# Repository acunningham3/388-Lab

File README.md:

# 388-Lab
Group Members:
Adam Cunningham,
Ryan McCarthy,
James McCarthy

Topic:
Automated Greenhouse Management System
  
  This is the repository for every lab report for our group.

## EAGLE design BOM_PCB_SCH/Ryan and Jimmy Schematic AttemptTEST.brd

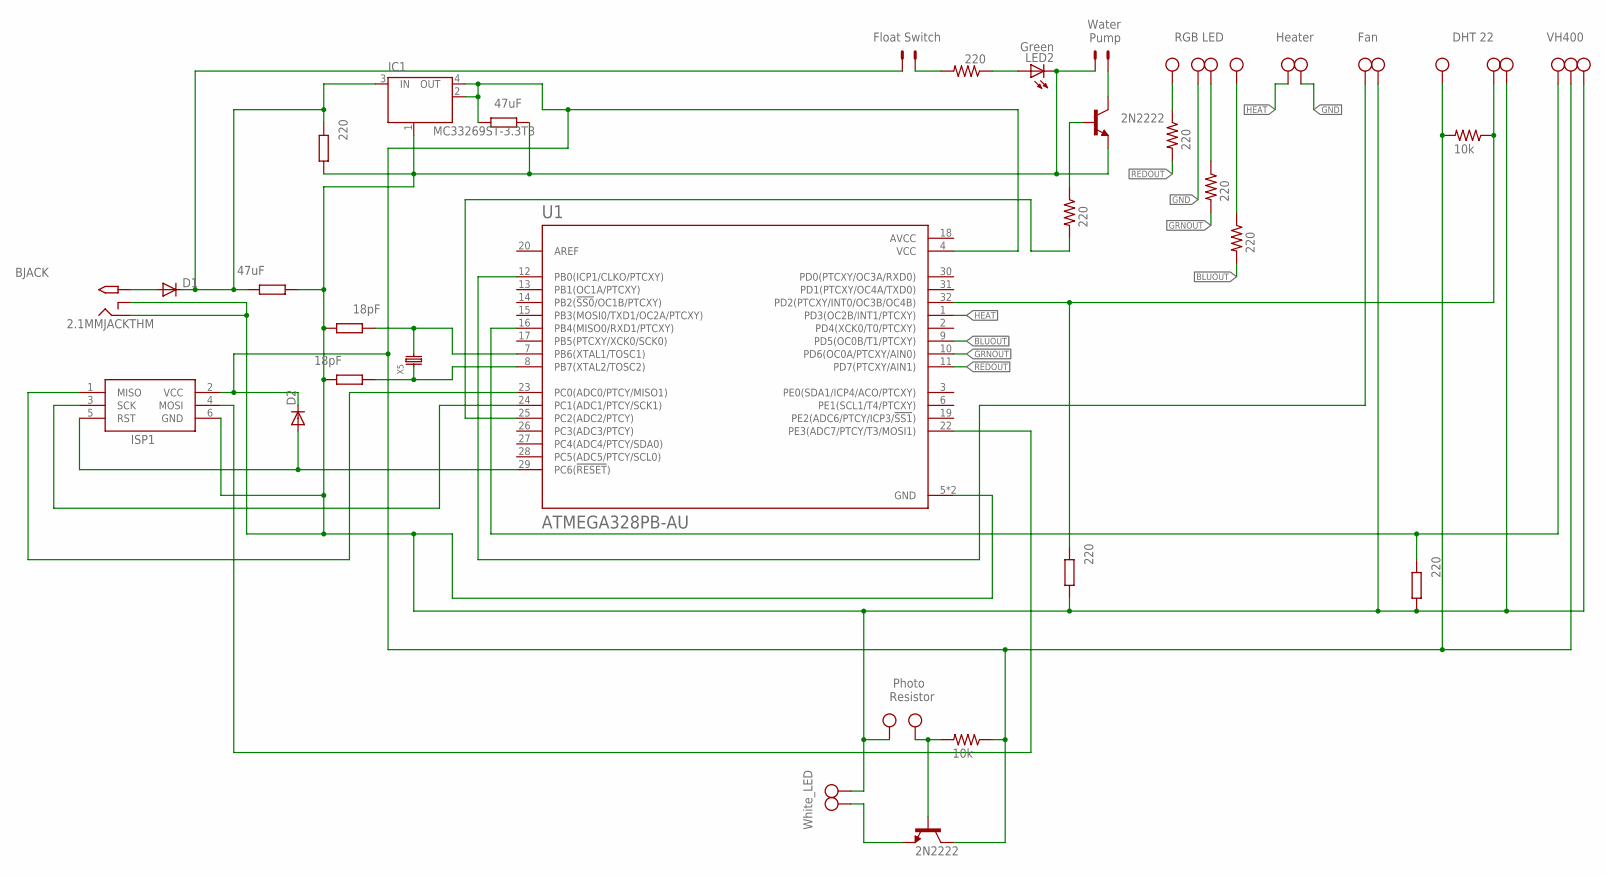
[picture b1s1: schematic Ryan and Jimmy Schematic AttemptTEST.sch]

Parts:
BJACK: 2.1MMJACKTHM; PJ-102A
C1, C6, C11: 220; M0805
C3, C8: 47uF; M0805
C9, C12: 18pF; M0805
D1, D2: DIODE-DO214BA; DO214BA
IC1: MC33269ST-3.3T3; SOT223
ISP1: AVRISP-6; AVRISP
LED2: Green; CHIPLED_0805
R1, R2, R4, R6, R7: 220; R0805
R3, R8: 10k; R0805
T1, T2: 2N2222; TO18
U1: ATMEGA328PB-AU; QFP80P900X900X120-32N
X1, X3: 1X03_5MM_SCREW; W237-103
X2, X4, X6, X8: 1X02_5MM_SCREW; W237-102
X5: ECS-80-18-5PX-TR; HC49/US
X7: W237-4
X9, X10: 332-02

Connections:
5V: C3.2, D2.C, IC1.2 (OUT), IC1.4 (OUT), ISP1.2 (VCC), R3.1, R8.2, T2.3 (C), U1.4 (VCC), X1.3, X3.2
AVCC: U1.18 (AVCC)
B: R7.1, X7.1
BLUOUT: R7.2, U1.9 (PD5(OC0B/T1/PTCXY))
DHT: C6.2, R8.1, U1.32 (PD2(PTCXY/INT0/OC3B/OC4B)), X1.2
FAN: U1.12 (PB0(ICP1/CLKO/PTCXY)), X8.2
F_S: R1.2, X10.1
G: R6.1, X7.2
GND: BJACK.RING, BJACK.RING_SW, C1.1, C3.1, C6.1, C8.1, C9.2, C11.1, C12.2, IC1.1 (GND/ADJ), ISP1.6 (GND), LED2.C, T1.1 (E), U1.5 (GND), U1.21 (GND), X1.1, X2.2, X3.1, X4.1, X6.2, X7.3, X8.1, X9.1
GRNOUT: R6.2, U1.10 (PD6(OC0A/PTCXY/AIN0))
HEAT: U1.1 (PD3(OC2B/INT1/PTCXY)), X4.2
MISO: ISP1.1 (MISO), U1.23 (PC0(ADC0/PTCY/MISO1))
MOSI: ISP1.4 (MOSI), U1.22 (PE3(ADC7/PTCY/T3/MOSI1))
unnamed: LED2.A, R1.1
PHOTO: R3.2, T2.2 (B), X2.1
POUT: R4.2, U1.25 (PC2(ADC2/PTCY))
PUMP: T1.3 (C), X9.2
PWRIN: BJACK.TIP, D1.A
P_CON: R4.1, T1.2 (B)
R: R2.1, X7.4
REDOUT: R2.2, U1.11 (PD7(PTCXY/AIN1))
RESET: D2.A, ISP1.5 (RST), U1.29 (PC6(!RESET!))
SCK: ISP1.3 (SCK), U1.24 (PC1(ADC1/PTCY/SCK1))
VH400: C11.2, U1.16 (PB4(MISO0/RXD1/PTCXY)), X3.3
VIN: C1.2, C8.2, D1.C, IC1.3 (IN), X10.2
WHT_LED: T2.1 (E), X6.1
XTAL1: C9.1, U1.7 (PB6(XTAL1/TOSC1)), X5.P$2 (XOUT)
XTAL2: C12.1, U1.8 (PB7(XTAL2/TOSC2)), X5.P$1 (XIN)

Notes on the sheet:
Fan
Heater
DHT 22
RGB LED
Water Pump
Float Switch
VH400
White_LED
Photo Resistor

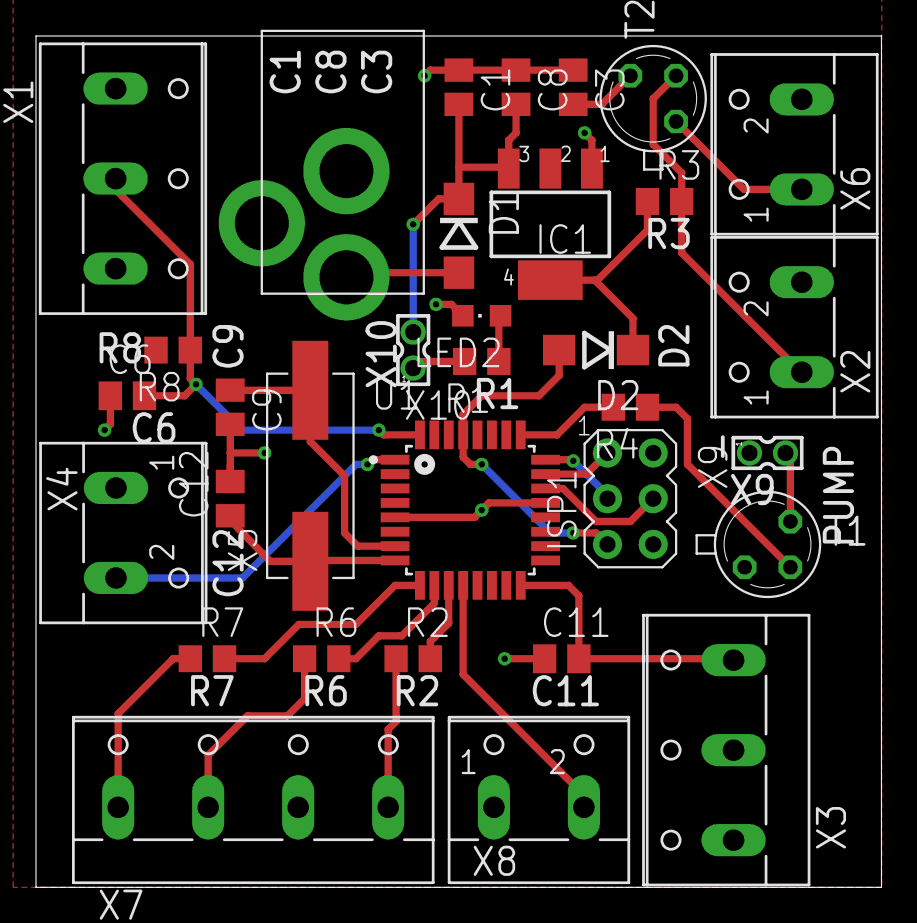
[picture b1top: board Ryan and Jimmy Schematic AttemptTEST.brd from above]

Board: 2 copper layers, 47.0 x 47.3 mm, 33 parts (0 on the bottom side), 27 nets.

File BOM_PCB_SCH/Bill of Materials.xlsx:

Qty | Value | Device | Package | Parts | Description | AVAILABILITY | DESCRIPTION | MF | MP | MPN | OC_FARNELL | OC_NEWARK | PACKAGE
4 |  | 1X02_5MM_SCREW | W237-102 | X2
2 |  | 1X03_5MM_SCREW | W237-103 | X1
2 |  | DIODE-DO214BA | DO214BA | D1
1 |  | ECS-80-18-5PX-TR | HC49/US | X5
1 |  | W237-4 | W237-4 | X7 | WAGO SCREW CLAMP |  |  |  |  |  | unknown | unknown
2 | 10k | R-US_R0805 | R0805 | R3
2 | 18pF | R-EU_M0805 | M0805 | C9
1 | 2.1MMJACKTHM | 2.1MMJACKTHM | PJ-102A | BJACK | 2.1mm x 5.5mm THM DC jack with internal switch. Digikey part #PJ-102A
3 | 220 | R-EU_M0805 | M0805 | C1
5 | 220 | R-US_R0805 | R0805 | R1
2 | 2N2222 | 2N2222 | TO18 | T1
2 | 332-02 | 332-02 | 332-02 | X9
2 | 47uF | R-EU_M0805 | M0805 | C3
1 | ATMEGA328PB-AU | ATMEGA328PB-AU | QFP80P900X900X120-32N | U1 | ATmega Series 20 MHz 32 KB Flash 2 KB SRAM 8-Bit Microcontroller - TQFP-32 | Unavailable | AVR microcontroller | EEPROM: 1024B | SRAM: 2kB | Flash: 32kB | TQFP32 | Microchip | ATMEGA328PB-AU
1 | AVRISP-6 | AVRISP-6 | AVRISP | ISP1 | AVR ISP HEADER
1 | Green | LEDCHIPLED_0805 | CHIPLED_0805 | LED2 | LED
1 | MC33269ST-3.3T3 | MC33269ST-3.3T3 | SOT223 | IC1 | Adjustable Output Low Dropout Voltage Regulator 800 mA

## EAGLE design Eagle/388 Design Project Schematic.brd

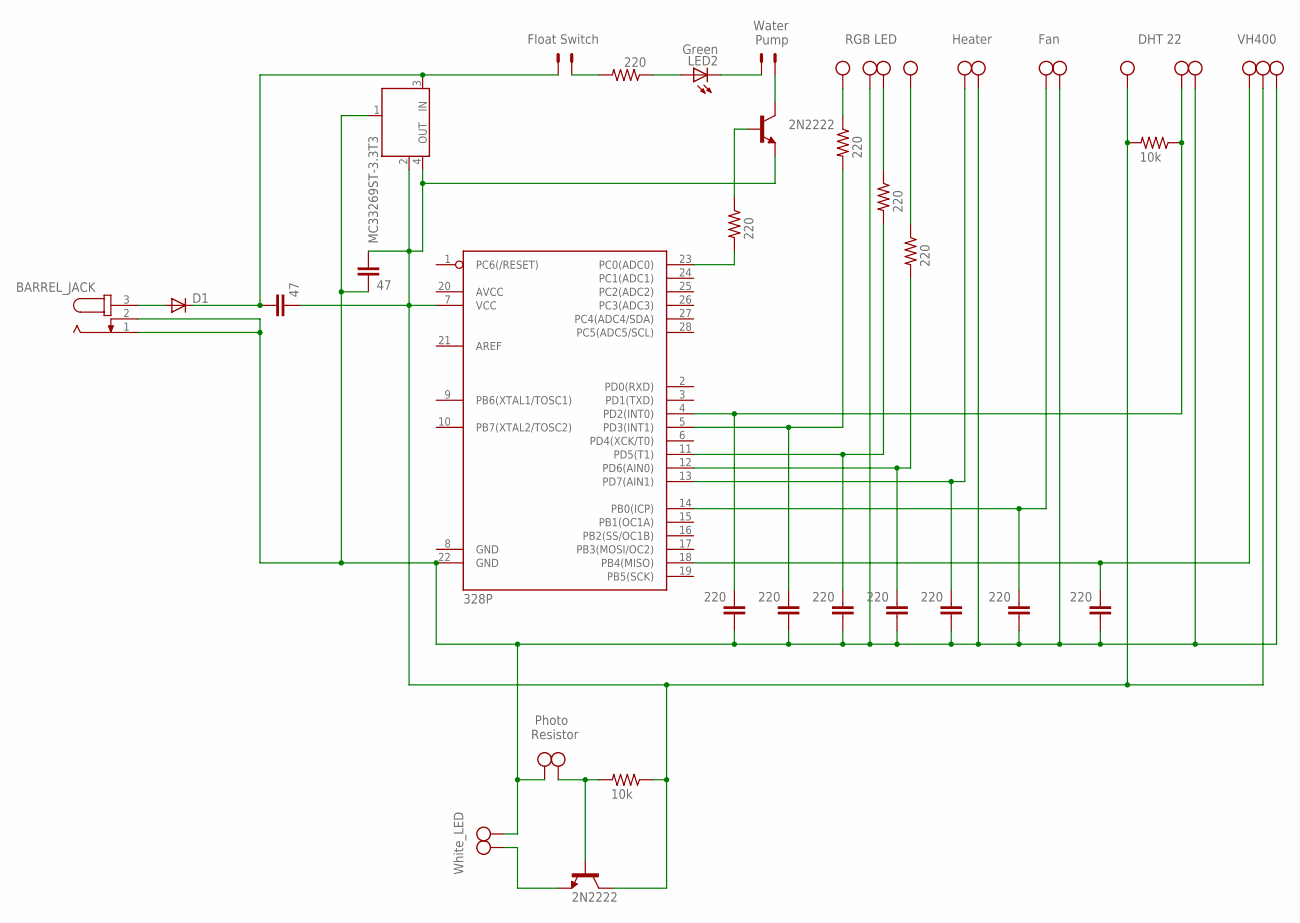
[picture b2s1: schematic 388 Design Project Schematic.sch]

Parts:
BARREL_JACK: JACK-PLUG1; SPC4078
C2, C4, C5, C6, C7, C10, C11: 220; C025-024X044
C8, C9: 47; C025-024X044
D1: DIODE-DO214BA; DO214BA
IC1: MC33269ST-3.3T3; SOT223
LED2: Green; CHIPLED_0805
R1, R2, R4, R6, R7: 220; R0805
R3, R8: 10k; R0805
T1, T2: 2N2222; TO18
U1: 328P; DIP28
WHITE_LED: AK300/2
X1, X2, X3: AK300/2
X4: Screw Hole 1; SMKDSP_1,5/4
X6: W237-103
X7: AK300/3
X9, X10: 332-02

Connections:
unnamed: BARREL_JACK.3, D1.A
unnamed: R2.1, X4.1
unnamed: T2.1 (E), WHITE_LED.1
unnamed: R3.2, T2.2 (B), X2.2
unnamed: R4.2, U1.23 (PC0(ADC0))
unnamed: BARREL_JACK.1, BARREL_JACK.2, C2.1, C4.1, C5.1, C6.1, C7.1, C9.2, C10.1, C11.1, IC1.1 (GND/ADJ), U1.22 (GND), WHITE_LED.2, X1.2, X2.1, X3.2, X4.2, X6.1, X7.1
unnamed: C8.2, C9.1, IC1.2 (OUT), IC1.4 (OUT), R3.1, R8.2, T1.1 (E), T2.3 (C), U1.7 (VCC), X6.3, X7.2
unnamed: C11.2, U1.18 (PB4(MISO)), X7.3
unnamed: C7.2, R2.2, U1.5 (PD3(INT1))
unnamed: C10.2, U1.14 (PB0(ICP)), X3.1
unnamed: R4.1, T1.2 (B)
unnamed: C5.2, R7.2, U1.12 (PD6(AIN0))
unnamed: C4.2, R6.2, U1.11 (PD5(T1))
unnamed: R6.1, X4.3
unnamed: R7.1, X4.4
unnamed: LED2.C, X9.1
unnamed: T1.3 (C), X9.2
unnamed: LED2.A, R1.1
unnamed: R1.2, X10.1
unnamed: C8.1, D1.C, IC1.3 (IN), X10.2
unnamed: C6.2, R8.1, U1.4 (PD2(INT0)), X6.2
unnamed: C2.2, U1.13 (PD7(AIN1)), X1.1

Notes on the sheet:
Fan
Heater
DHT 22
RGB LED
Water Pump
Float Switch
VH400
White_LED
Photo Resistor

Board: 2 copper layers, 32 parts (0 on the bottom side), 22 nets, no tracks yet.

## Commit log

2018-09-18 Create Lab Report
2018-09-18 Update Lab Report
2018-10-04 Rename Lab Report to Lab-Report-1
2018-10-04 Create Lab-Report-2
2018-10-04 Update Lab-Report-2
2018-10-17 Create Lab-Report-3
2018-10-17 Update Lab-Report-3
2018-10-26 Create Prototype Code
2018-11-07 Update Prototype Code
2018-11-09 Create Eagle Schematic

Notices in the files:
parts and their libraries:
SparkFun-IC-Microcontroller: Licensing: Creative Commons ShareAlike 4.0 International - https://creativecommons.org/licenses/by-sa/4.0
